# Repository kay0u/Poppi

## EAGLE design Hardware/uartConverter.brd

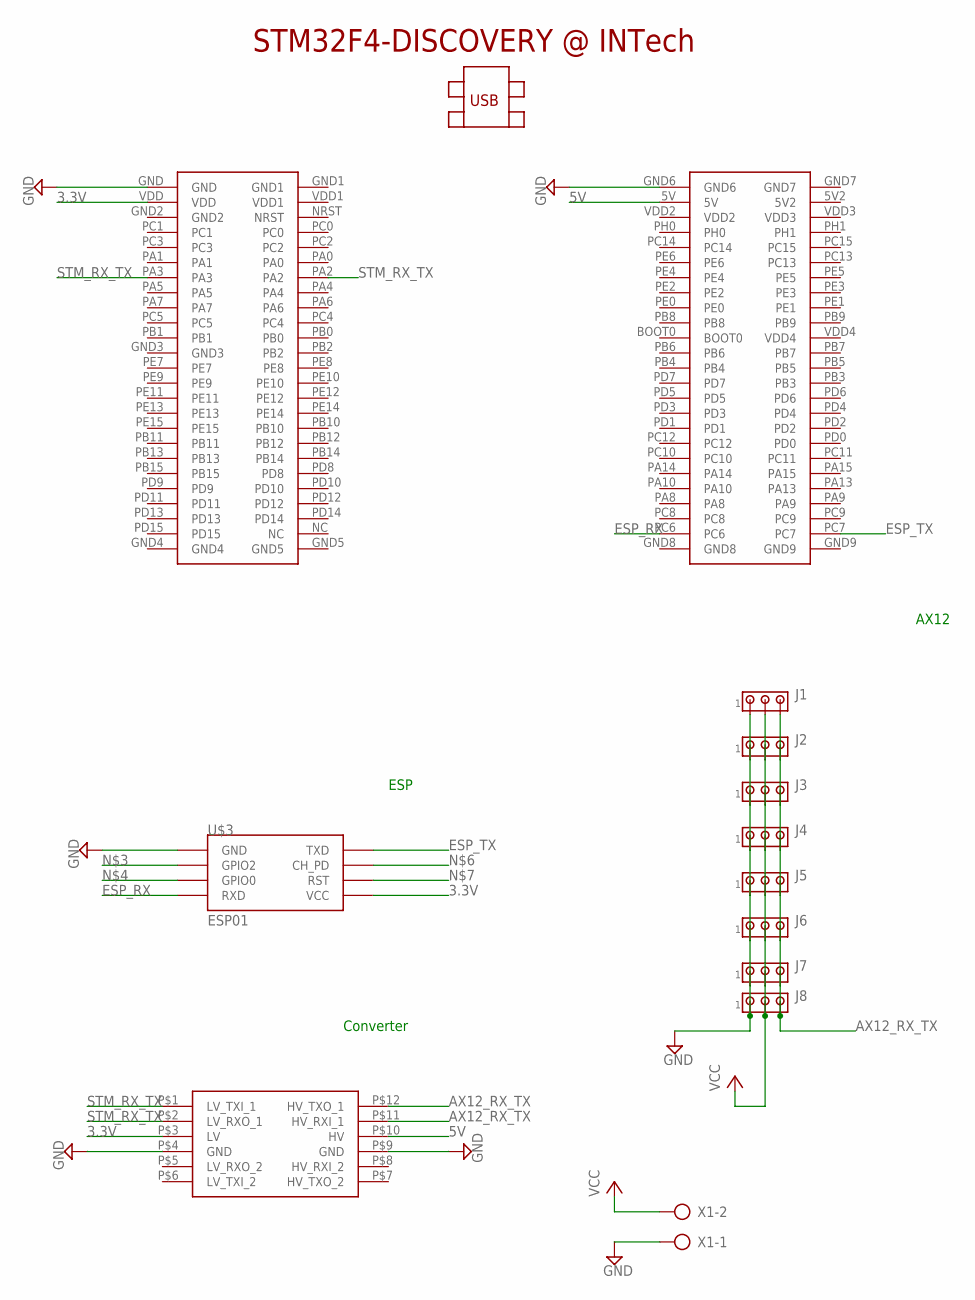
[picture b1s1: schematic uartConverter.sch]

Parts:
J1, J2, J3, J4, J5, J6, J7, J8: MTA03-100; 10X03MTA
U$1: LOGIC_LEVEL_CONVERTER
U$2: STM32F4-DISCOVERY
U$3: ESP01
X1: AK300/2

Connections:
3.3V: U$1.P$3 (LV), U$2.VDD, U$3.VCC
5V: U$1.P$10 (HV), U$2.5V
AX12_RX_TX: J1.3, J2.3, J3.3, J4.3, J5.3, J6.3, J7.3, J8.3, U$1.P$11 (HV_RXI_1), U$1.P$12 (HV_TXO_1)
ESP_RX: U$2.PC6, U$3.RX (RXD)
ESP_TX: U$2.PC7, U$3.TX (TXD)
GND: J1.1, J2.1, J3.1, J4.1, J5.1, J6.1, J7.1, J8.1, U$1.P$4 (GND), U$1.P$9 (GND), U$2.GND, U$2.GND6, U$3.GND, X1.1
STM_RX_TX: U$1.P$1 (LV_TXI_1), U$1.P$2 (LV_RXO_1), U$2.PA2, U$2.PA3
VCC: J1.2, J2.2, J3.2, J4.2, J5.2, J6.2, J7.2, J8.2, X1.2

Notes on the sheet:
ESP
AX12
Converter

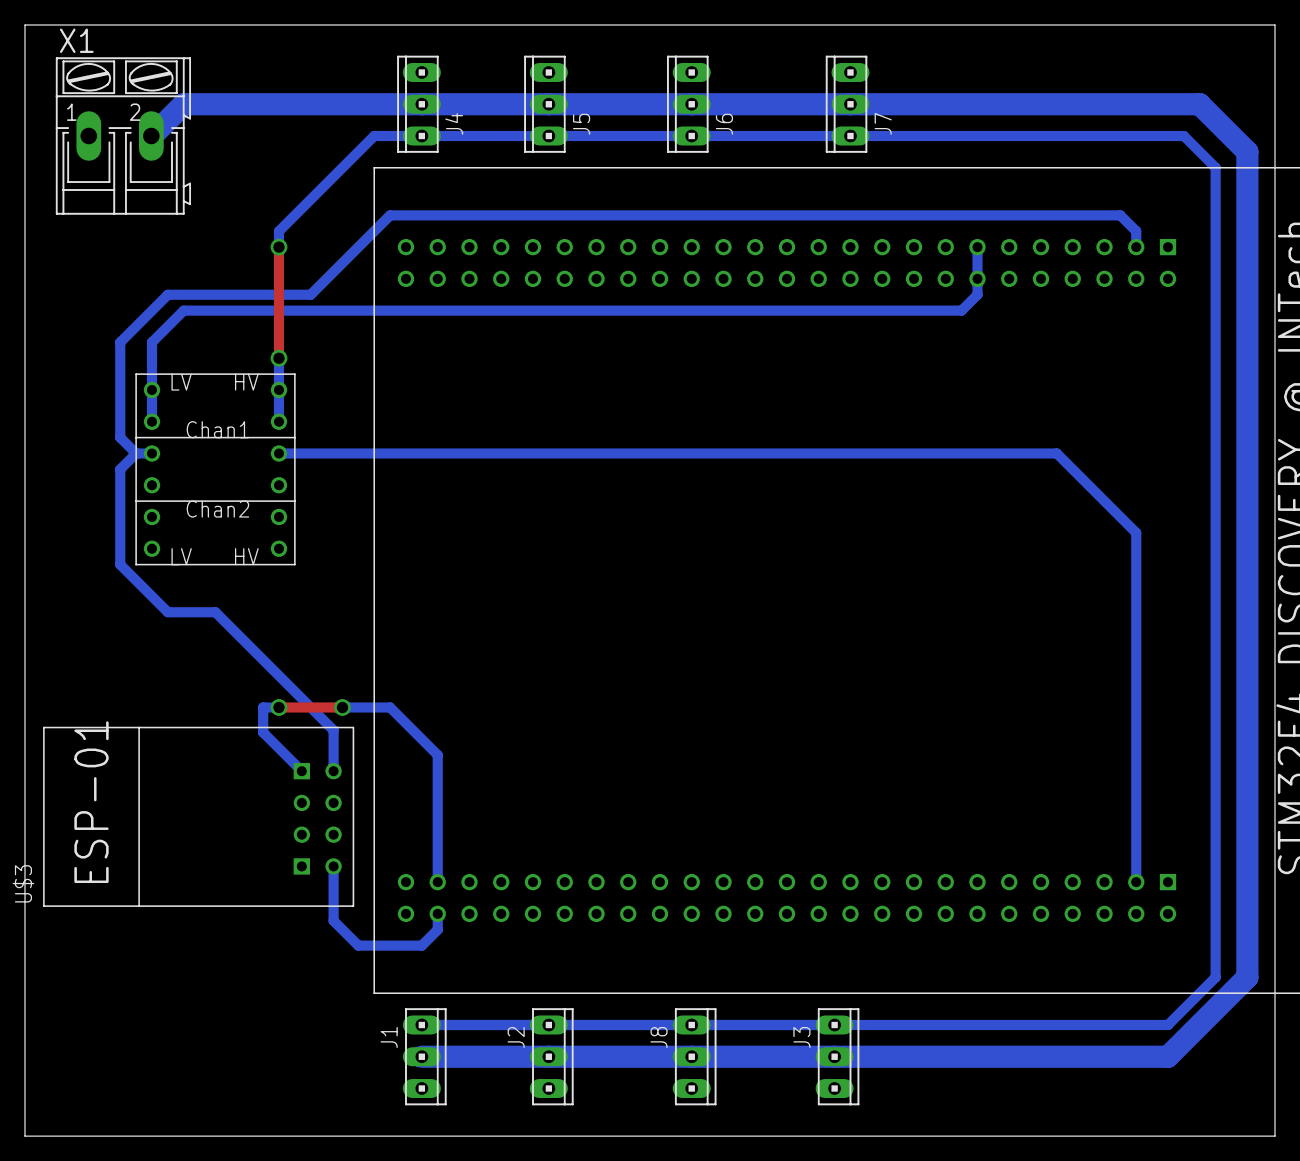
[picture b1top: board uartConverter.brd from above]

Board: 2 copper layers, 100.0 x 88.9 mm, 12 parts (0 on the bottom side), 8 nets.

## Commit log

2015-06-15 Validation initiale pour ajouter les fichiers .gitIgnore et .gitAttribute par défaut.
2015-06-15 Initial commit, code accelero + gyro
2015-06-18 Ajout de Useful et Imu
    Encapsulation de l'accéléro et du gyro dans la classe Imu.
    Nettoyage de LEDBlink grâce à Useful.
2015-06-18 Includes yay !
2015-06-18 Plus propre et sans spam de printf. Le filtre marche pas.
2015-06-20 Ajout Time qui fonctionne pas.
2015-06-20 gitignore
2015-06-20 Accelerometer angle formated.
2015-06-20 Added square macro + error handling in extern.
2015-06-20 Ajout de freeRTOS
2015-06-20 Merge
2015-06-20 Gitignore avec un nouveau git index ?
2015-06-20 Suppression des fichiers de conf
2015-06-20 Complementary filter now works fine.
2015-06-20 rm cached
2015-06-20 rm cached ce qui reste
2015-06-20 Changements mineurs, nettoyage essentiellement.
2015-06-20 Revert "Changements mineurs, nettoyage essentiellement."
    This reverts commit bcfe4d44c936d4b8d3746817040d3a59d92f31b4.
2015-06-20 Ajout d'un 3eme thread
2015-06-20 Pardon
2015-06-21 Un peu de doc parce que j'suis un mec bien.
2015-06-21 Changement de chemins
2015-06-21 Thread qui fonctionnent... Et print de la merde.
2015-07-30 Mise à jour pour être compatible avec eclipse
2015-07-30 Ajout de la lib stm
2015-07-30 Exclusion des fichiers heap_x.c
2015-07-30 Patch d'un probleme avec l'initialisation hardware
2015-08-14 Update de la lib HAL de stm + ajout du code pour la série
2015-08-14 Fonction read bloquant (il faudra choisir ce dont on a besoin)
2015-12-30 Code des AX12 (à tester)
2016-01-05 Ajout de Vector3
2016-01-05 Ajout de Trigo
2016-01-06 Ajout de .settings dans gitignore
2016-01-06 Ajout des classes hexapode (et enfants) et legs. Amélioration de Vector3
2016-01-06 Patch Ax12.hpp
2016-01-06 MAJ de la lib stm32f4-hal -> 1.10.1
2016-01-06 Trigo et Vector3 sont maintenant des .h et .cpp
2016-01-07 Ajout des gait et début des séquences de mouvements
2016-01-07 Cycle de movements à intégrer dans une task avec un sleep.
2016-01-08 Les arrays en C, c'est vraiment chouette.
2016-01-08 Thread dans Gait pour controler la marche (à tester avec une série...
2016-01-09 Déplacement des fichiers de la lib stm + petite modif pour la série Unity
2016-01-09 Modification de la lib CMSIS, et ajout de lib maths (comme arm_cos_f32 par ex)
2016-01-09 Fix init leg & (void*)Gait dans thread
2016-01-09 Ménage
2016-01-09 Création du mutex à la création de de Gait et ajour de preprocessor pour le printf()
2016-01-09 Ajout de print debug qui appelle printf en debug seulement
2016-01-10 Ajout de LedController et LedColor pour controller les Led plus facilement
2016-01-10 Rename et nettoyage du main
2016-01-10 Thread de Gait en cours.
2016-01-10 Changement de mode de la série
2016-01-10 Ca devrait fonctionner maintenant
2016-01-10 Correction d'un crash
2016-01-11 send_char fonctionne
2016-01-12 Test pour AX12
2016-01-12 Allegement du code de la série
2016-01-12 Meme modif pour le read
2016-01-12 Ajout du projet Unity
2016-01-12 Echanges de messages
2016-01-12 La led rouge n'est allumé qu'en cas d'erreur
2016-01-12 Problème dans le read
2016-01-17 IK : La simulation et le code STM donnent les même résultatet gamma est dans le même repère des deux côtés. Servo : Ajout des angles limite pour Gamma
2016-01-17 Angles mesurés, SetGoal bloquant
2016-01-17 Add des fichiers Unity
2016-01-18 Gait task fonctionne. Vive les std::array.
2016-01-19 Serial avec des queues en RX et en TX
2016-01-19 Utilisation de osMutex au lieu de xSemaphore
2016-03-16 Schema elec
2016-05-15 routage
2017-02-06 Correction de quelques petits soucis avec la série
2017-02-11 Transfert du projet sur VisualGDB
2017-02-11 AX12 getPosition fonctionne
2017-02-11 Refactor de la lib AX12 et ajout de quelques fonctions (Elles ont toutes été testées)
2017-02-12 Amélioration de la lib AX12
2017-02-12 Amélioration de la lib ax12 et ajout de méthodes
2017-02-12 Same
2017-02-12 Je ne sais pas trop si je vais garder ces vectors. Ca me parait un peu trop...
2017-02-12 GetTorqueLimit && SetTorqueLimit
2017-02-12 Visiblement attendre ne sert à rien ici. Si jamais on a des bugs, faudra revert ce commit
2017-02-13 Maj de la scene Unity qui marche maintenant. En gros.
2017-02-13 Fix du lien serial/dropdown
2017-02-16 Ajout des fonctions syncWrite pour faire bouger plusieurs AX12 en même temps
2017-02-18 Ajout de setExtremum
2017-04-05 Ajout du sln
2017-04-05 Correction du path
2017-04-05 filters
2017-04-06 releaseMutex if ID = 0xFE
2017-04-08 Supression du projet unity. Ajout de UnitySerial avec un protocol
2017-04-08 Maj de la lib stm
2017-04-09 Ajout du semihosting, et update de la syntaxe des mutex
2017-04-09 Correction du normalized si le vecteur est (0,0,0)
2017-04-09 Fix un bug dans le consructeur de l'hexapode
2017-04-09 Oups
2017-04-16 ajout du serial print log et implementation de stop() dans Servo
2017-04-16 Transmission du code d'erreur pour les Get... des AX12
2017-04-16 Gestion des erreurs AX12
2017-04-17 Gestion du magnétomètre (enfin)
2017-04-17 get temperature
2017-09-09 Correction d'includes et maj du projet
2017-09-09 Correction d'un potentiel crash à cause du magnetomètre
2017-09-09 Limitation des AX12 en angle sur les pattes
2017-09-09 Blink de la led rouge en cas de crash
2017-09-09 Petites modifs
2017-09-09 IK fonctionnel! (Il y a des constantes à refactor...)
2017-09-10 Correctif sur le vcxproje et le filter
2017-09-10 MAJ de freeRTOSConfig (9.0)
2017-09-10 Simplification du main Thread
2017-09-10 Refactor des AX12 (Séparation de la logique et de la transmission)
2017-09-10 Implémentation partielle de reachedTarget
2017-09-10 vcxproj & filter
2017-09-10 Vrai waitForMoveEnd
2017-09-23 Rerefactor des Ax12 (je vais arriver à quelque chose qui me plait)
2017-09-23 std::array pour les datas de l'imu
2018-05-18 update toolchain + repair semihosting \o/
2018-05-20 test
2018-05-20 fix ax12
2018-05-20 make libAx12 great again!
2018-05-20 checksum is not a data to copy
2018-06-04 Fix a AX12Base::SetId explanation
2018-06-05 default destructor

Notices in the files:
parts and their libraries:
SparkFun-Boards: Licensing: Creative Commons ShareAlike 4.0 International - https://creativecommons.org/licenses/by-sa/4.0
